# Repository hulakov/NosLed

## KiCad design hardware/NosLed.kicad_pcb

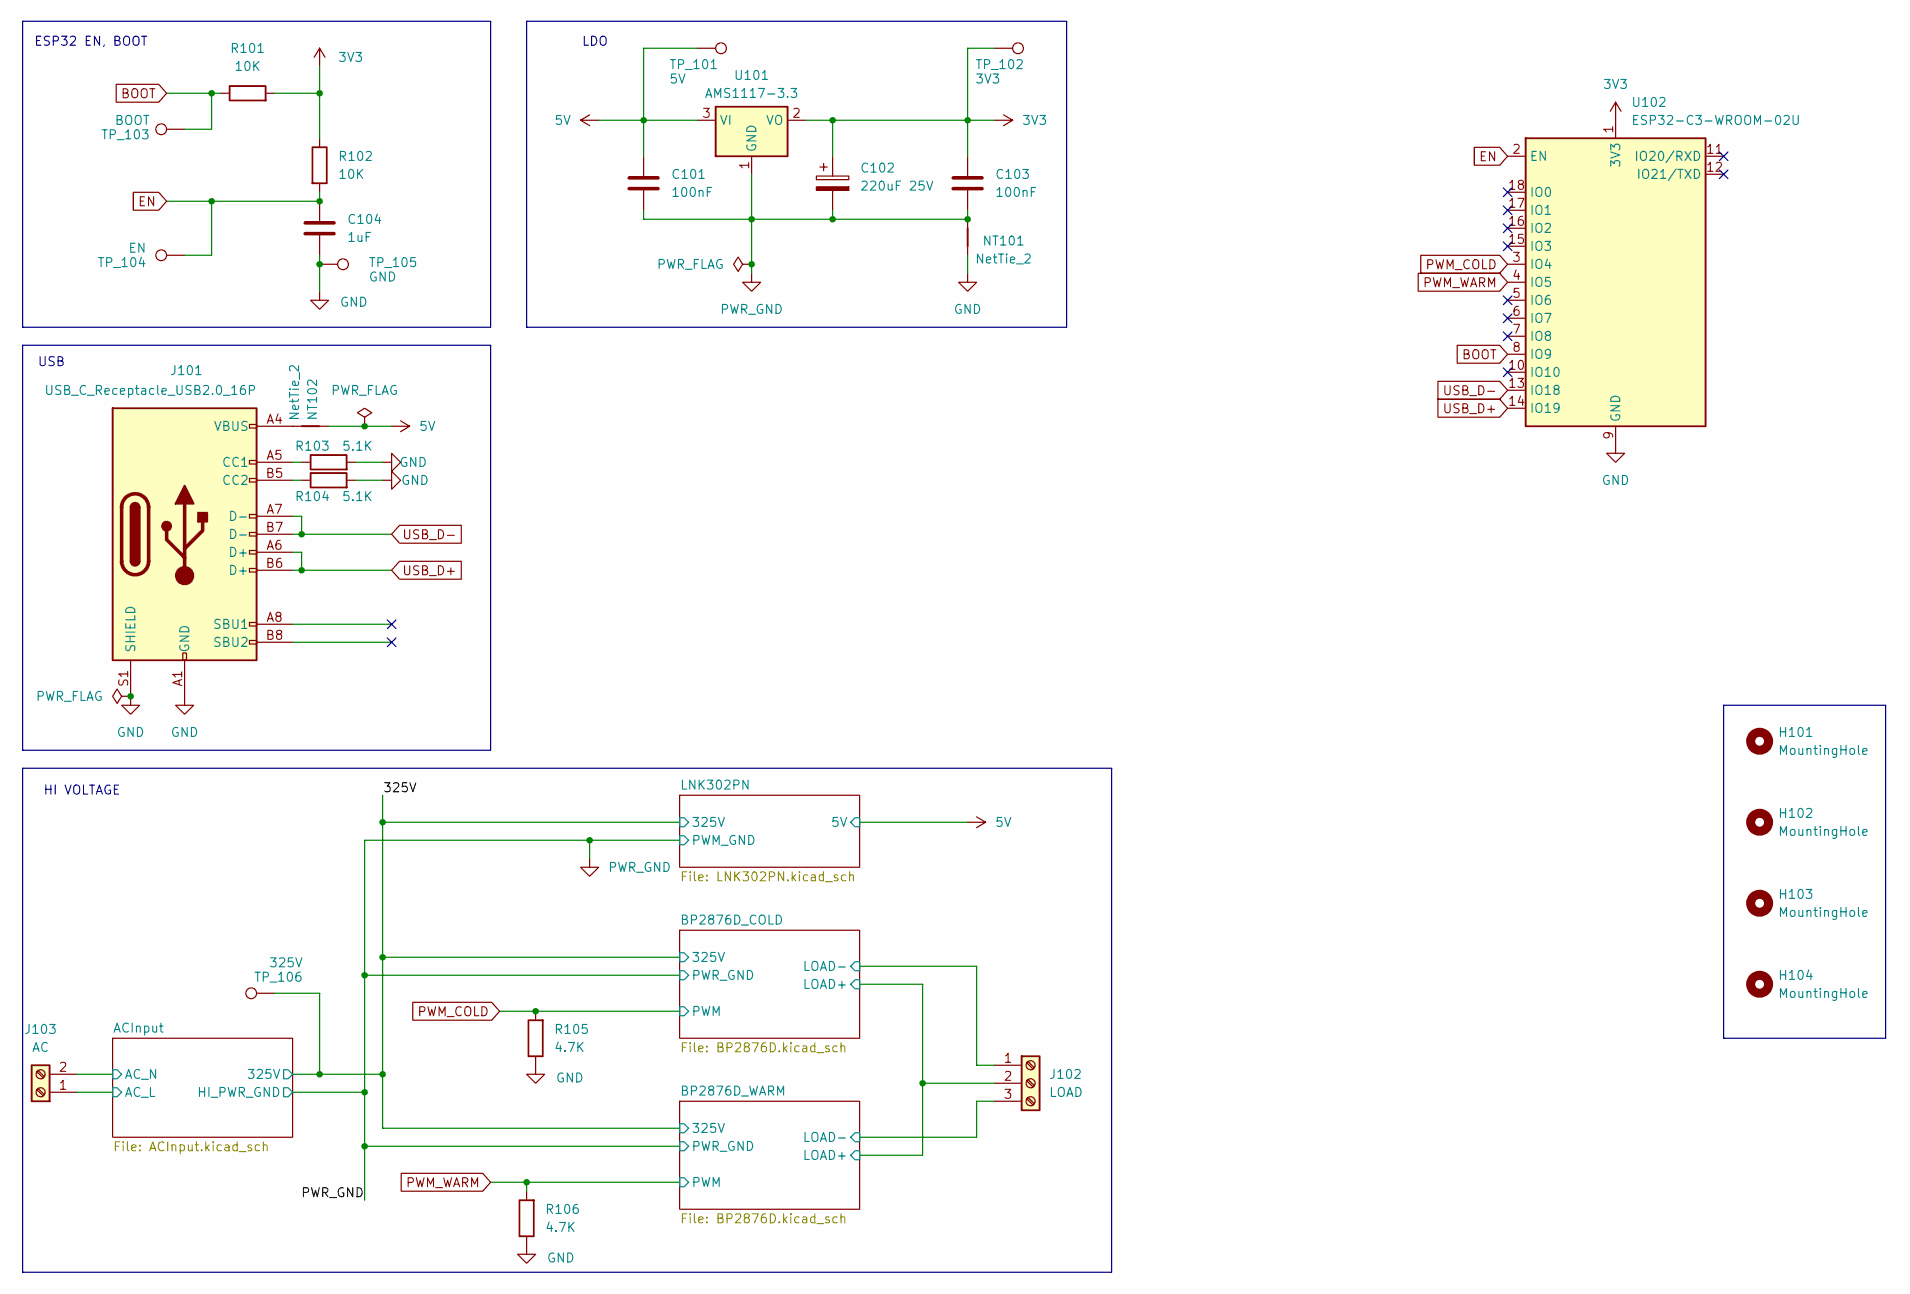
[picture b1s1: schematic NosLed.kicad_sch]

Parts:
C101, C103: 100nF; C_0603_1608Metric
C102: 220uF 25V; CP_Radial_D6.3mm_P2.50mm
C104: 1uF; C_0805_2012Metric
H101, H102, H103, H104: MountingHole; MountingHole_3.2mm_M3
J101: USB_C_Receptacle_USB2.0_16P; USB_C_Receptacle_HRO_TYPE-C-31-M-12
J102: LOAD; TerminalBlock_Phoenix_MKDS-1,5-3-5.08_1x03_P5.08mm_Horizont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
J103: AC; TerminalBlock_Phoenix_MKDS-1,5-2-5.08_1x02_P5.08mm_Horizont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
NT101, NT102: NetTie_2; NetTie-2_SMD_Pad0.5mm
R101, R102: 10K; R_0603_1608Metric
R103, R104: 5.1K; R_0603_1608Metric
R105, R106: 4.7K; R_0603_1608Metric
TP_101: 5V; TestPoint_Pad_1.0x1.0mm
TP_102: 3V3; TestPoint_Pad_1.0x1.0mm
TP_103: BOOT; TestPoint_Pad_1.0x1.0mm
TP_104: EN; TestPoint_Pad_1.0x1.0mm
TP_105: GND; TestPoint_Pad_1.0x1.0mm
TP_106: 325V; TestPoint_Pad_1.0x1.0mm
U101: AMS1117-3.3; SOT-223-3_TabPin2
U102: ESP32-C3-WROOM-02U

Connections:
3V3: C102.1, C103.2, R101.2, R102.1, TP_102.1, U101.2 (VO), U102.1 (3V3)
5V: C101.2, NT102.2, TP_101.1, U101.3 (VI); also elsewhere on the board
/325V: J102.2, TP_106.1; also elsewhere on the board
/ACInput/AC_L: J103.1; also elsewhere on the board
/ACInput/AC_N: J103.2; also elsewhere on the board
/BP2876D_COLD/LOAD-: J102.1; also elsewhere on the board
/BP2876D_WARM/LOAD-: J102.3; also elsewhere on the board
BOOT: R101.1, TP_103.1, U102.8 (IO9)
EN: C104.1, R102.2, TP_104.1, U102.2 (EN)
GND: C104.2, J101.A1 (GND), J101.A12 (GND), J101.B1 (GND), J101.B12 (GND), J101.S1 (SHIELD), NT101.2, R103.2, R104.2, R105.1, R106.1, TP_105.1, U102.9 (GND), U102.19 (GND); also elsewhere on the board
unnamed: J101.A5 (CC1), R103.1
unnamed: J101.B5 (CC2), R104.1
unnamed: J101.A4 (VBUS), J101.A9 (VBUS), J101.B4 (VBUS), J101.B9 (VBUS), NT102.1
PWM_COLD: R105.2, U102.3 (IO4); also elsewhere on the board
PWM_WARM: R106.2, U102.4 (IO5); also elsewhere on the board
PWR_GND: C101.1, C102.2, C103.1, NT101.1, U101.1 (GND); also elsewhere on the board
USB_D+: J101.A6 (D+), J101.B6 (D+), U102.14 (IO19)
USB_D-: J101.A7 (D-), J101.B7 (D-), U102.13 (IO18)

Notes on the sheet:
LDO
ESP32 EN, BOOT
HI VOLTAGE
USB

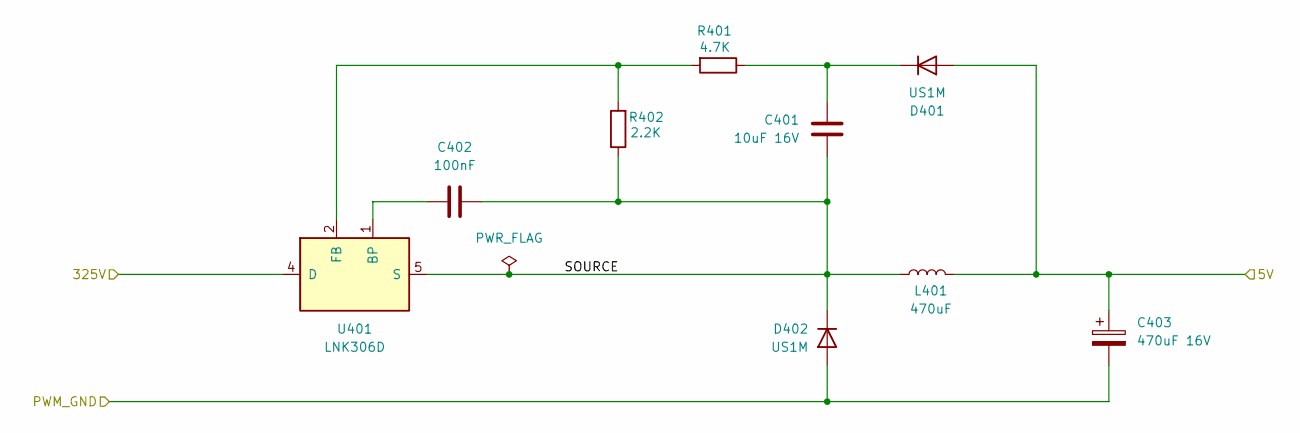
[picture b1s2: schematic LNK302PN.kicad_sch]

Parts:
C401: 10uF 16V; C_0805_2012Metric
C402: 100nF; C_0603_1608Metric
C403: 470uF 16V; CP_Radial_D8.0mm_P5.00mm
D401, D402: US1M; D_SMA
L401: 470uF; L_Radial_D9.5mm_P5.00mm_Fastron_07HVP
R401: 4.7K; R_0603_1608Metric
R402: 2.2K; R_0603_1608Metric
U401: LNK306D; LNK302PN-SOIC-8_3.9x4.9mm_P1.27mm

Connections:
5V: C403.1, D401.2 (A), L401.2; also elsewhere on the board
/325V: U401.4 (D); also elsewhere on the board
/LNK302PN/SOURCE: C401.1, C402.1, D402.1 (K), L401.1, R402.1, U401.5 (S), U401.6 (S), U401.7 (S), U401.8 (S)
unnamed: C401.2, D401.1 (K), R401.1
unnamed: C402.2, U401.1 (BP)
unnamed: R401.2, R402.2, U401.2 (FB)
PWR_GND: C403.2, D402.2 (A); also elsewhere on the board

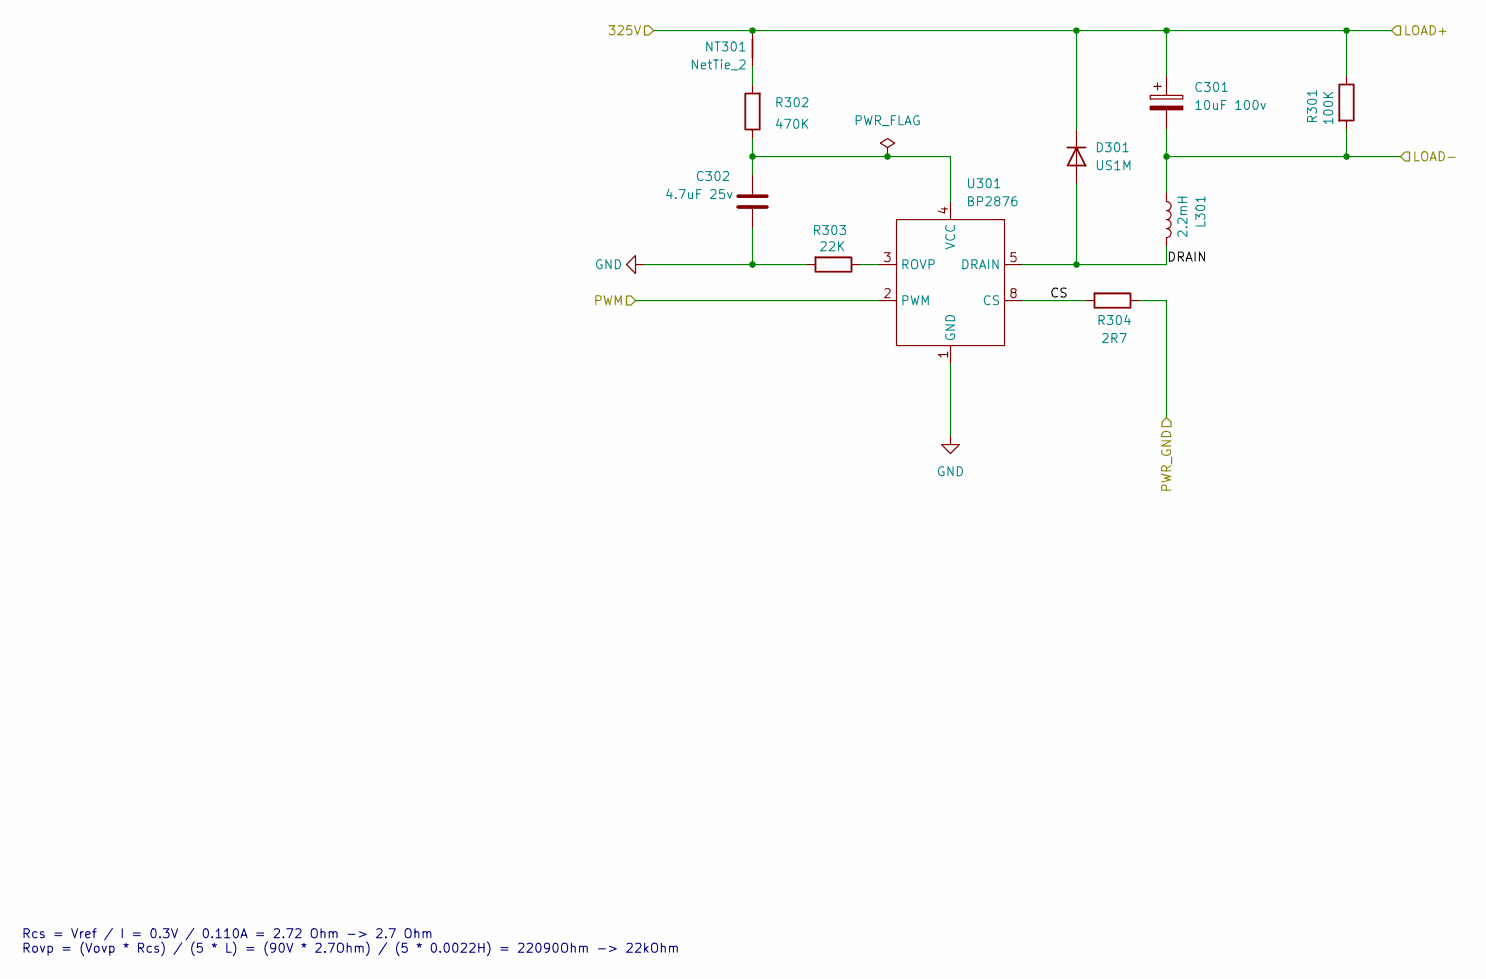
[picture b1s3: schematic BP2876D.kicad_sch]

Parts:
C301: 10uF 100v; CP_Radial_D6.3mm_P2.50mm
C302: 4.7uF 25v; C_0805_2012Metric
D301: US1M; D_SMA
L301: 2.2mH; L_Radial_D9.5mm_P5.00mm_Fastron_07HVP
NT301: NetTie_2; NetTie-2_SMD_Pad0.5mm
R301: 100К; R_1206_3216Metric
R302: 470K; R_2512_6332Metric
R303: 22K; R_0603_1608Metric
R304: 2R7; R_0805_2012Metric
U301: BP2876; SOIC-8-N7_3.9x4.9mm_P1.27mm

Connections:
/325V: C301.1, D301.1 (K), NT301.2, R301.1; also elsewhere on the board
/BP2876D_WARM/CS: R304.2, U301.8 (CS)
/BP2876D_WARM/DRAIN: D301.2 (A), L301.2, U301.5 (DRAIN), U301.6 (DRAIN)
/BP2876D_WARM/LOAD-: C301.2, L301.1, R301.2; also elsewhere on the board
GND: C302.2, R303.2, U301.1 (GND); also elsewhere on the board
unnamed: NT301.1, R302.2
unnamed: R303.1, U301.3 (ROVP)
unnamed: C302.1, R302.1, U301.4 (VCC)
PWM_WARM: U301.2 (PWM); also elsewhere on the board
PWR_GND: R304.1; also elsewhere on the board

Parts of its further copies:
C501: 10uF 100v; CP_Radial_D6.3mm_P2.50mm
C502: 4.7uF 25v; C_0805_2012Metric
D501: US1M; D_SMA
L501: 2.2mH; L_Radial_D9.5mm_P5.00mm_Fastron_07HVP
NT501: NetTie_2; NetTie-2_SMD_Pad0.5mm
R501: 100К; R_1206_3216Metric
R502: 470K; R_2512_6332Metric
R503: 22K; R_0603_1608Metric
R504: 2R7; R_0805_2012Metric
U501: BP2876; SOIC-8-N7_3.9x4.9mm_P1.27mm

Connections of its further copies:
/325V: C501.1, D501.1 (K), NT501.2, R501.1; also elsewhere on the board
/BP2876D_COLD/CS: R504.2, U501.8 (CS)
/BP2876D_COLD/DRAIN: D501.2 (A), L501.2, U501.5 (DRAIN), U501.6 (DRAIN)
/BP2876D_COLD/LOAD-: C501.2, L501.1, R501.2; also elsewhere on the board
GND: C502.2, R503.2, U501.1 (GND); also elsewhere on the board
unnamed: NT501.1, R502.2
unnamed: R503.1, U501.3 (ROVP)
unnamed: C502.1, R502.1, U501.4 (VCC)
PWM_COLD: U501.2 (PWM); also elsewhere on the board
PWR_GND: R504.1; also elsewhere on the board

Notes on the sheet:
Rcs = Vref / I = 0.3V / 0.110A = 2.72 Ohm -> 2.7 Ohm Rovp = (Vovp * Rcs) / (5 * L) = (90V * 2.7Ohm) / (5 * 0.0022H) = 22090Ohm -> 22kOhm

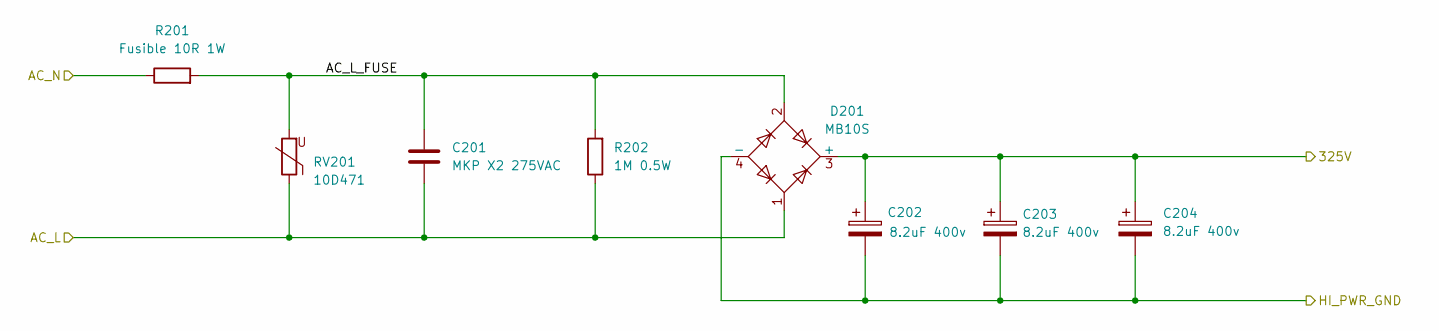
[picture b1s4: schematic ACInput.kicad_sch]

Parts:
C201: MKP X2 275VAC; C_Rect_L13.0mm_W6.0mm_P10.00mm_FKS3_FKP3_MKS4
C202, C203, C204: 8.2uF 400v; CP_Radial_D8.0mm_P3.50mm
D201: MB10S; TO-269AA
R201: Fusible 10R 1W; R_Axial_DIN0414_L11.9mm_D4.5mm_P15.24mm_Horizontal
R202: 1M 0.5W; R_2512_6332Metric
RV201: 10D471; RV_Disc_D12mm_W4.8mm_P7.5mm

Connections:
/325V: C202.1, C203.1, C204.1, D201.3 (+); also elsewhere on the board
/ACInput/AC_L: C201.2, D201.1, R202.1, RV201.1; also elsewhere on the board
/ACInput/AC_L_FUSE: C201.1, D201.2, R201.2, R202.2, RV201.2
/ACInput/AC_N: R201.1; also elsewhere on the board
PWR_GND: C202.2, C203.2, C204.2, D201.4 (-); also elsewhere on the board

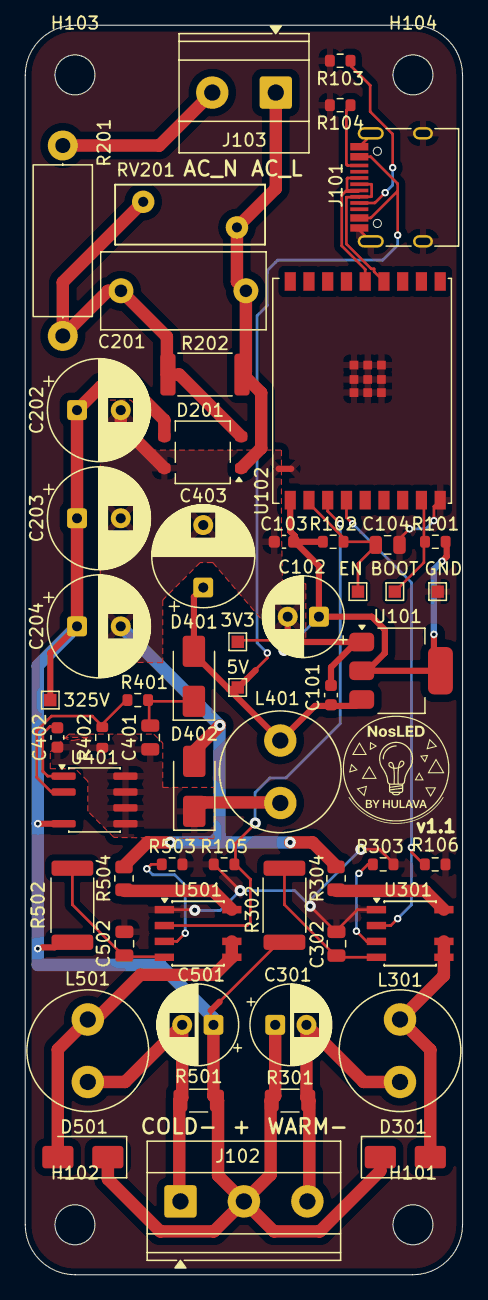
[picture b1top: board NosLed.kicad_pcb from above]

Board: 2 copper layers, 35.0 x 100.0 mm, 64 parts (0 on the bottom side), 33 nets.

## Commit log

2026-02-04 AC Input
2026-02-04 BP2876D
2026-02-04 LNK302PN
2026-02-04 BP2956XS
2026-02-06 Prototype
2026-02-08 Tracing draft
2026-02-11 Tracing 0.2
2026-02-11 Version 1
2026-02-27 Fixes
2026-02-27 Use non-hand soldering footprints
2026-03-18 v1.1
2026-03-18 Hotfixes
2026-04-08 Fix holes
